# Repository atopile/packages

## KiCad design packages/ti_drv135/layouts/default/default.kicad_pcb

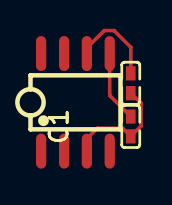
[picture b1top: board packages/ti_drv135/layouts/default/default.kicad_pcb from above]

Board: 2 copper layers, 3 parts (0 on the bottom side), 3 nets.

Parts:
C1, C2: 1µF ±10% 25V X5R; C0402
U1: SOIC-8_L5.0-W4.0-P1.27-LS6.0-BL

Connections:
VCC: C2.1, U1.6
negative_power-GND: C1.2, U1.5
positive_power-GND: C1.1, C2.2, U1.3

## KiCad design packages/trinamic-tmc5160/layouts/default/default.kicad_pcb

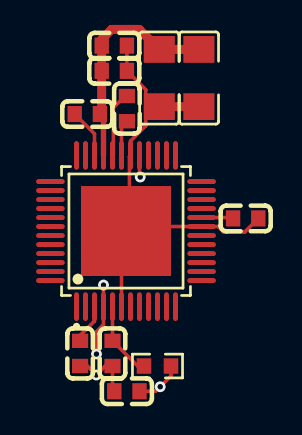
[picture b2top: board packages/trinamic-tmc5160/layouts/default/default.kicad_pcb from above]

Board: 2 copper layers, 12 parts (0 on the bottom side), 9 nets.

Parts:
C1, C2: {4.229..5.17}F; C0603
C3: 2.2±10.0%F; C0603
C4: {8.999..1.1}F; C0603
C5, C6, C9, C10: 1±10.0%F; C0603
C7, C8: {8.999..1.1}F; C1206
R1: 2.2±1.0%Ω; R0603
U1: TQFP-48_L7.0-W7.0-P0.50-LS9.0-BL-EP

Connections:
cap_5v-power-hv: C1.1, R1.1, U1.5
cap_cp-power-hv: C3.1, U1.32
cap_vcc-power-hv: C4.1, R1.2, U1.29
cap_vccio-power-hv: C5.1, U1.20
cap_vcp-power-hv: C6.1, U1.34
gnd: C1.2, C2.2, C4.2, C5.2, C7.2, C8.2, C9.2, C10.2, U1.6, U1.19, U1.30, U1.49
hv: C2.1, U1.3
lv: C3.2, U1.31
power_motor_10uf_caps[1]-power-hv: C6.2, C7.1, C8.1, C9.1, C10.1, U1.33

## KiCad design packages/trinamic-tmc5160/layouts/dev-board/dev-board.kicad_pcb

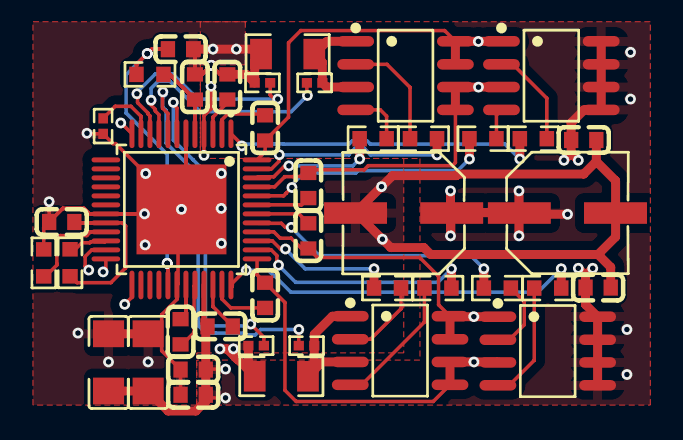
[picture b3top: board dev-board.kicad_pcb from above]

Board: 2 copper layers, 41 parts (0 on the bottom side), 42 nets.

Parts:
C1, C2, C3, C4: {1.979..2.42}F; C0603
C5, C6: 4.7±10.0%F; C0603
C7, C8: {4.229..5.17}F; C0603
C9: 2.2±10.0%F; C0603
C10: {8.999..1.1}F; C0603
C11, C12, C15, C16: 1±10.0%F; C0603
C13, C14: {8.999..1.1}F; C1206
C17, C18: {3.759..5.64}F; CAP-SMD_BD6.3-L6.6-W6.6-LS7.6-FD
Q1, Q2, Q3, Q4: SOIC-8_L4.9-W3.9-P1.27-LS6.0-BL
R1, R2, R3, R4, R15, R16, R17, R18: 22±1.0%Ω; R0603
R5, R12: 10000±1.0%Ω; R0603
R6, R7: 0.075±1.0%Ω; R1206
R8, R9, R10, R11: 47±0.1%Ω; R0402
R13: 0Ω; R0402
R14: 2.2±1.0%Ω; R0603
U1: TQFP-48_L7.0-W7.0-P0.50-LS9.0-BL-EP

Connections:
1: R15.1, U1.1
36: R2.1, U1.36
38: R4.1, U1.38
39: R3.1, U1.39
41: R1.1, U1.41
44: R16.1, U1.44
46: R18.1, U1.46
47: R17.1, U1.47
SD_MODE: R5.1, U1.21
SPI_MODE: R12.1, U1.22
SRAH_P: R8.1, U1.8
SRAL_N: R9.1, U1.7
SRBH_P: R10.1, U1.9
SRBL_N: R11.1, U1.10
TST_MODE: R13.1, U1.11
bootstrap_capacitors[1]-power-hv: C2.1, U1.35
bootstrap_capacitors[2]-power-hv: C3.1, U1.2
bootstrap_capacitors[3]-power-hv: C4.1, U1.43
cap_cp-power-hv: C9.1, U1.32
cap_vcp-power-hv: C12.1, U1.34
full_bridge_a-high_gate_2-gate: Q1.4, R2.2
full_bridge_a-low_gate_1-gate: Q2.2, R3.2
full_bridge_a-low_gate_2-gate: Q2.4, R4.2
full_bridge_b-bridge_power-lv: Q4.1, Q4.3, R7.1, R10.2
full_bridge_b-high_gate_1-gate: Q3.2, R15.2
full_bridge_b-high_gate_2-gate: Q3.4, R16.2
full_bridge_b-low_gate_1-gate: Q4.2, R17.2
full_bridge_b-low_gate_2-gate: Q4.4, R18.2
gate: Q1.2, R1.2
gnd: C5.2, C6.2, C7.2, C8.2, C10.2, C11.2, C13.2, C14.2, C15.2, C16.2, C17.2, C18.2, R5.2, R6.2, R7.2, R9.2, R11.2, R13.2, U1.6, U1.19, U1.30, U1.49
hv: C1.1, U1.42
lv: Q2.1, Q2.3, R6.1, R8.2
motor-a1: C1.2, Q1.1, Q2.7, Q2.8, U1.40
motor-a2: C2.2, Q1.3, Q2.5, Q2.6, U1.37
motor-b1: C3.2, Q3.1, Q4.7, Q4.8, U1.48
motor-b2: C4.2, Q3.3, Q4.5, Q4.6, U1.45
power-lv: C9.2, U1.31
power_5v_out-hv: C7.1, R14.1, U1.5
power_12v_out-hv: C8.1, U1.3
power_vcc-hv: C10.1, R14.2, U1.29
power_vccio-hv: C11.1, R12.2, U1.20
power_vsa-hv: C5.1, C6.1, C12.2, C13.1, C14.1, C15.1, C16.1, C17.1, C18.1, Q1.5, Q1.6, Q1.7, Q1.8, Q3.5, Q3.6, Q3.7, Q3.8, U1.4, U1.33

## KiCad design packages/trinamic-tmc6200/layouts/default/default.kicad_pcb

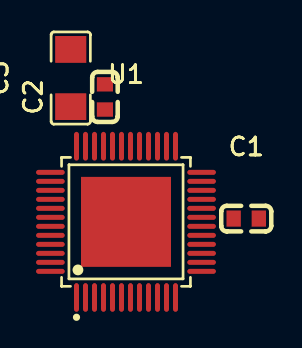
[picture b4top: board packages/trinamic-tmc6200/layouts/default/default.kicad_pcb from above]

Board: 2 copper layers, 4 parts (0 on the bottom side), 3 nets, no tracks yet.

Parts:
C1, C2: 100nF ±10% 50V X7R; C0603
C3: 4.7µF ±10% 50V X7R; C1206
U1: TQFP-48_L7.0-W7.0-P0.50-LS9.0-BL-EP

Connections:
VCC_IO: C1.1, U1.19
gnd: C1.2, C2.2, C3.2, U1.2, U1.28, U1.31, U1.35, U1.40, U1.45
hv: C2.1, C3.1, U1.33

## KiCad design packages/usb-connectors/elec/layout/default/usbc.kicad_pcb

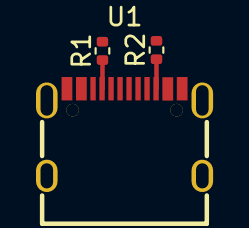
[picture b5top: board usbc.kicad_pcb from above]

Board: 2 copper layers, 3 parts (0 on the bottom side), 6 nets.

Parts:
R1, R2: Chip Resistor - Surface Mount 4.7KOhms ±5% 1/16W 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; R0402
U1: USB-C-SMD_KH-TYPE-C-16P

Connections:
cc1: R1.1, U1.A5
cc2: R2.1, U1.B5
dm: U1.A7, U1.B7
dp: U1.A6, U1.B6
gnd: R1.2, R2.2, U1.1, U1.2, U1.3, U1.4, U1.A1, U1.A12, U1.B1, U1.B12
vcc: U1.A4, U1.A9, U1.B4, U1.B9
